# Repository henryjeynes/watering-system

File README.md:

# watering-system

**This project is on hold for the moment. The boards, schematics, and code in this repo are not guaranteed to work. Please let me know if you have any questions about the project.**

Automatic watering system based on ATmegaxx8 microcontrollers.

Using the code or boards is not currently recommended for long-term use.

TODO:
(items in **bold** are scheduled for the next release. Items which have been dealt with are ~~struck through~~.)
  * Add EEPROM-stored settings, which can be changed over the serial port
  * Add sleep code for lower power consumption
  * ~~Add individual watering. The code currently uses one pump for both plants~~
  * Replace linear regulator with switching
  * Add optional float switch for water tank
  * Add optional voltage sensing for batteries (with settings for various chemistries)

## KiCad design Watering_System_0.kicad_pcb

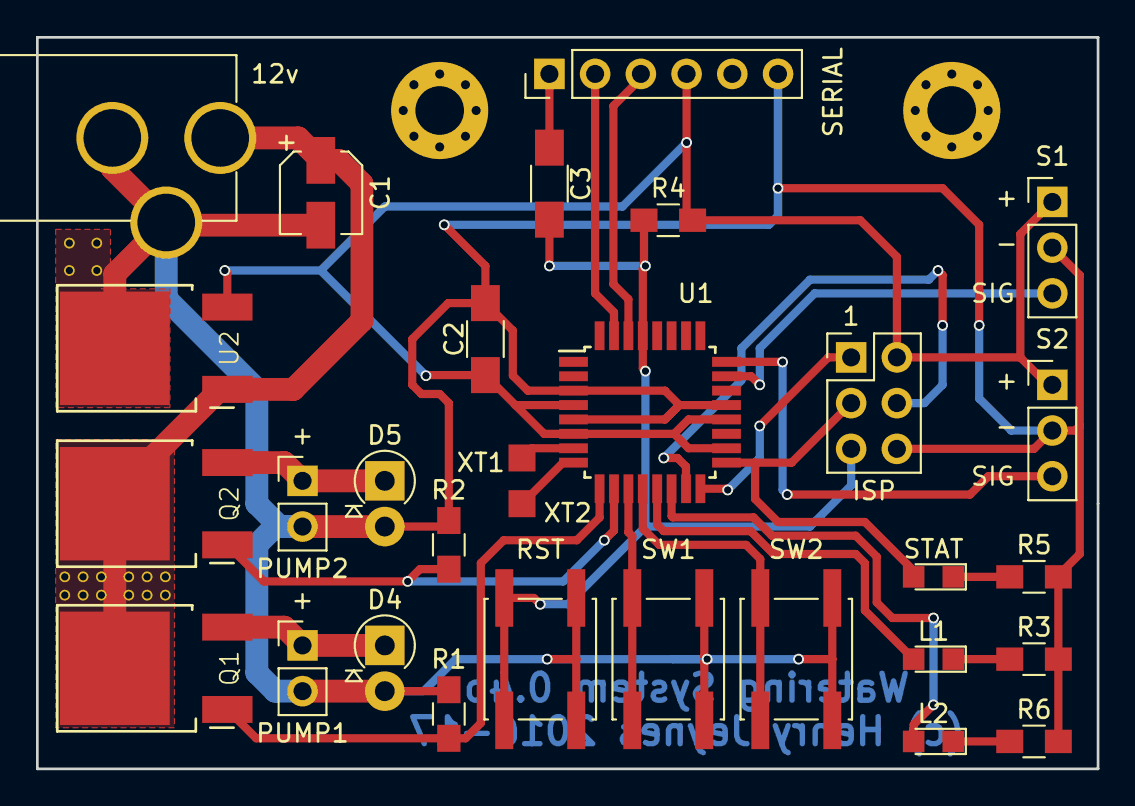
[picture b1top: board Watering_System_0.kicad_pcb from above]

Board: 2 copper layers, 58.9 x 40.6 mm, 30 parts (0 on the bottom side), 25 nets.

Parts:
12v: BARREL_JACK
C1: 4.7uF; CP_Elec_4x4.5
C2, C3: 100nF; C_1206_HandSoldering
D1: STAT; LED_0805
D2: L1; LED_0805
D3: L2; LED_0805
D4, D5: 1N4002; D_DO-41_SOD81_P2.54mm_Vertical_AnodeUp
J1: PUMP1; Pin_Header_Straight_1x02_Pitch2.54mm
J2: PUMP2; Pin_Header_Straight_1x02_Pitch2.54mm
J3: ISP; Pin_Header_Straight_2x03_Pitch2.54mm
J4: SERIAL; Pin_Header_Straight_1x06_Pitch2.54mm
J5: S1; Pin_Header_Straight_1x03_Pitch2.54mm
J6: S2; Pin_Header_Straight_1x03_Pitch2.54mm
Q1, Q2: FDD6630A; TO-252
R1, R2, R4: 10K; R_0805_HandSoldering
R3, R5, R6: 680; R_0805_HandSoldering
SW1, SW2, SW3: SPST_TACT-EVQQ2; SW_SPST_EVQQ2
TP1: XT1; Measurement_Point_Square-SMD-Pad_Small
TP2: XT2; Measurement_Point_Square-SMD-Pad_Small
U1: Mxx8; TQFP-32_7x7mm_Pitch0.8mm
U2: 78M05; TO-252

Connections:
+5V: C2.1, J3.2, J4.4, J5.1, J6.1, R4.2, U1.4, U1.6, U1.18, U1.20, U2.3
+12V: 12v.1, C1.1, Q1.2, Q2.2, U2.1
/L1: D2.2, U1.13
/L2: D3.2, U1.14
/MISO: J3.1, U1.16
/MOSI: J3.4, U1.15
/P1: Q1.1, R1.1, U1.9
/P2: Q2.1, R2.1, U1.10
/RST: C3.2, J3.5, R4.1, SW1.1, U1.29
/RX: J4.2, U1.31
/S1: J5.3, U1.23
/S2: J6.3, U1.24
/STAT: D1.2, J3.3, U1.17
/SW1: SW2.1, U1.11
/SW2: SW3.1, U1.12
/TX: J4.3, U1.30
GND: 12v.2, 12v.3, C1.2, C2.2, D4.2, D5.2, J1.2, J2.2, J3.6, J4.6, J5.2, J6.2, R1.2, R2.2, R3.2, R5.2, R6.2, SW1.2, SW2.2, SW3.2, U1.3, U1.5, U1.21, U2.2
unnamed: C3.1, J4.1
unnamed: D1.1, R5.1
unnamed: D2.1, R3.1
unnamed: D3.1, R6.1
unnamed: D4.1, J1.1, Q1.3
unnamed: D5.1, J2.1, Q2.3
unnamed: TP1.1, U1.7
unnamed: TP2.1, U1.8

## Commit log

2016-11-05 Added EAGLE files for Hydro 0.1b
    Hydro 0.1b adds the power jack which was missing in the unreleased 0.1a.
2016-11-05 Added Arduino files, version 0.1a
    These Arduino files are designed for the Hydro 0.1b. This version of the program is only intended for testing I/O, such as relays, LEDs, buttons, etc. This version should not be used for watering pla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
2016-11-05 Updated README.md
    Added warning about the incompleteness of the code and boards
2016-11-05 Create version-history
2016-11-05 New version, 0.1b2
    Minor update to 0.1b, mostly shorter idle blink for slightly lower power consumption
2016-11-05 Update version-history
2016-11-05 added BOM
2016-12-24 Update version-history
    Added 0.1c, not released yet
2016-12-24 Update version-history
    more details about 0.1c
2017-01-05 Uploaded Hydro 0.2a
2017-01-24 Added board version 0.3b
    Refer to version-history.txt for more info
2017-01-24 Update README.md
    Removed the line about adding MOSFETs. Version 0.3b now has built-in switching
2017-02-04 Added 0.3c
    0.2b had a minor design flaw which rendered the whole board useless.
2017-02-04 Rename 0_3cbrd.brd to 0_3c.brd
2017-02-27 Added board version 0.3d
2017-06-12 Edit README.md
    Due to some trouble with the code, EEPROM-stored settings will be released after the next version.
2017-06-12 Added board version 0.4b
    Current revision of 0.4b, may be changed later. Untested
